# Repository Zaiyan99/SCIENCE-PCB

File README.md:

# SCIENCE-PCB
This a PCB made for URC 2023 on behalf of Mongol-Tori. It interfaces some sensors to decrease wire complexity

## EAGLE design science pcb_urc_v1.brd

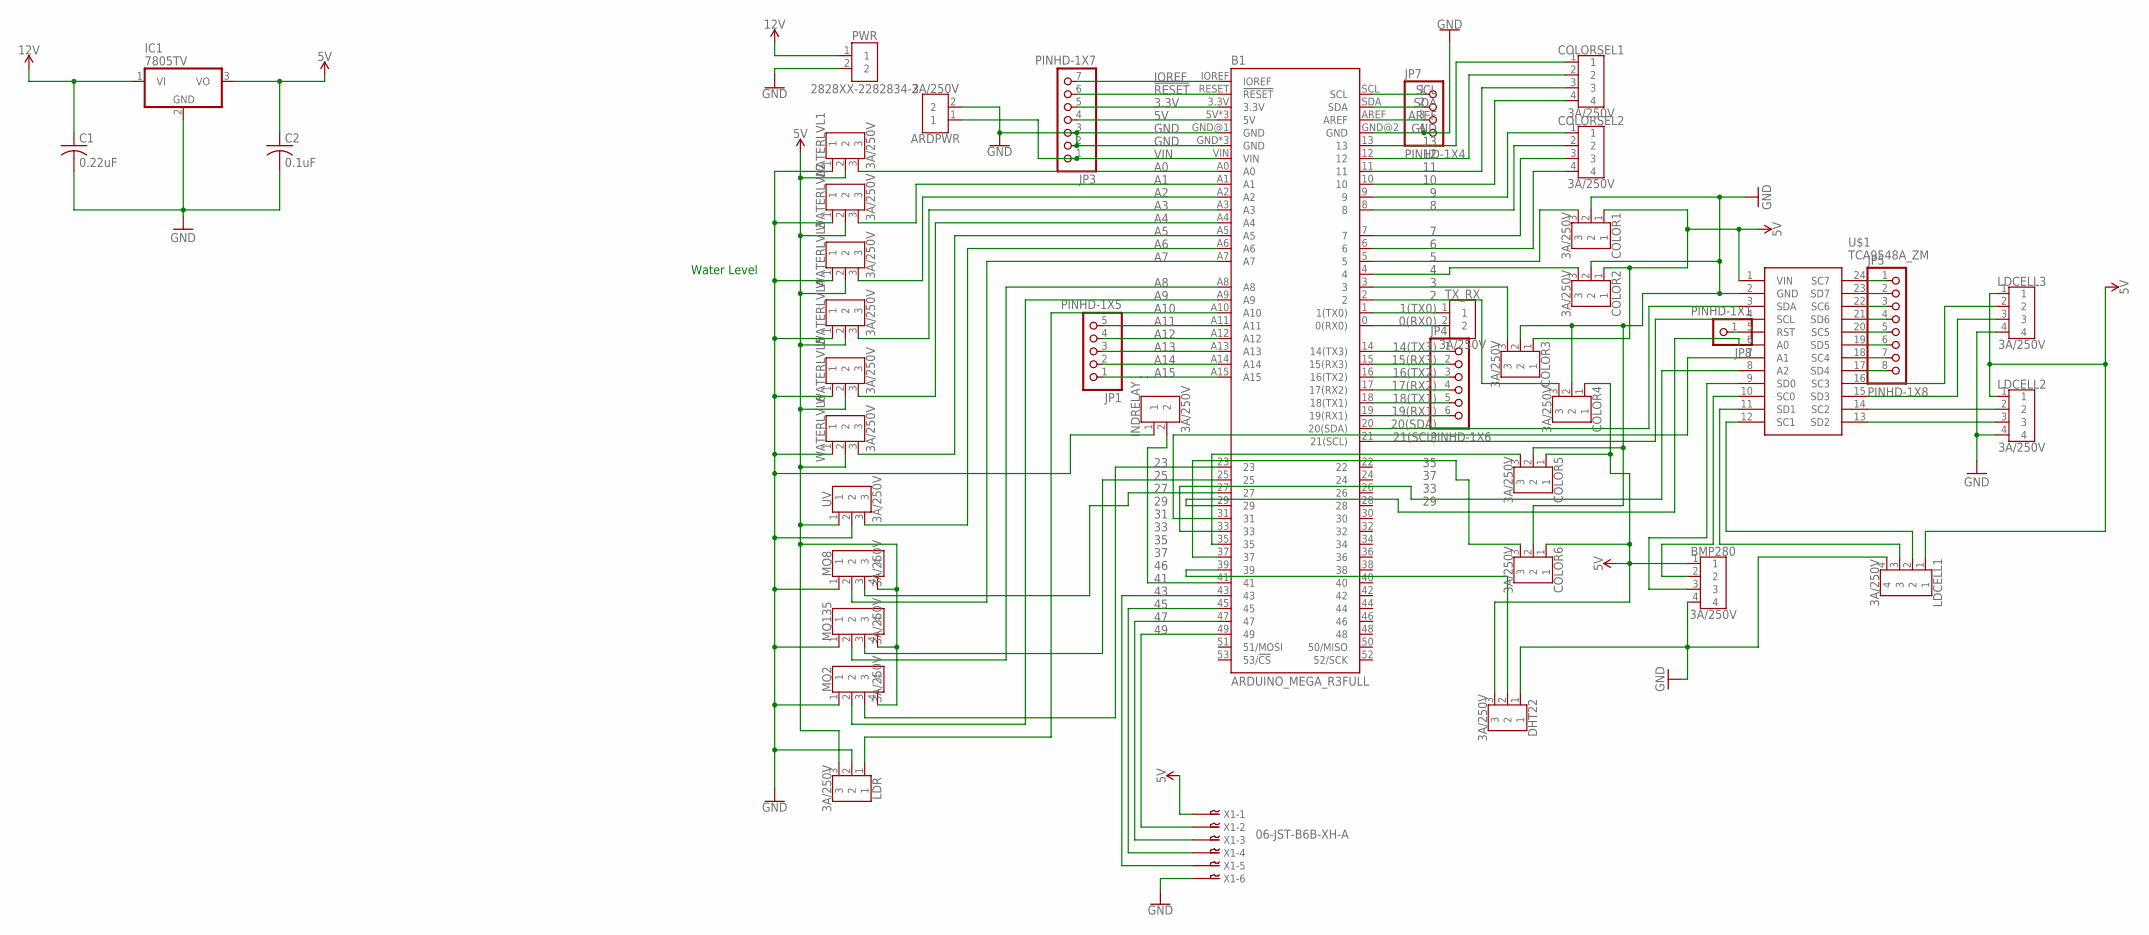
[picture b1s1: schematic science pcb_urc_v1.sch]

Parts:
ARDPWR: 3A/250V; B2B-XH-A
B1: ARDUINO_MEGA_R3FULL; ARDUINO_MEGA_NO_SILK
BMP280: 3A/250V; B4B-XH-A
C1: 0.22uF; C025-025X050
C2: 0.1uF; C025-025X050
COLOR1, COLOR2, COLOR3, COLOR4, COLOR5, COLOR6: 3A/250V; B3B-XH-A
COLORSEL1, COLORSEL2: 3A/250V; B4B-XH-A
DHT22: 3A/250V; B3B-XH-A
IC1: 7805TV; TO220V
INDRELAY: 3A/250V; B2B-XH-A
JP1: PINHD-1X5; 1X05
JP3: PINHD-1X7; 1X07
JP4: PINHD-1X6; 1X06
JP5: PINHD-1X8; 1X08
JP7: PINHD-1X4; 1X04
JP8: PINHD-1X1; 1X01
LDCELL1, LDCELL2, LDCELL3: 3A/250V; B4B-XH-A
LDR: 3A/250V; B3B-XH-A
MQ2, MQ8, MQ135: 3A/250V; B4B-XH-A
PWR: 2828XX-2282834-2; TERMBLK_254-2N
TX_RX: 3A/250V; B2B-XH-A
U$1: TCA9548A_ZM; 2717
UV: 3A/250V; B3B-XH-A
WATERLVL1, WATERLVL2, WATERLVL3, WATERLVL4, WATERLVL5, WATERLVL6: 3A/250V; B3B-XH-A
X1: 06-JST-B6B-XH-A; B6B-XH

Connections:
0(RX0): B1.0 (0(RX0)), TX_RX.2
1(TX0): B1.1 (1(TX0)), TX_RX.1
2: B1.2, COLOR4.3
3: B1.3, COLOR3.3
3.3V: B1.3.3V, JP3.5
4: B1.4, COLOR2.3
5: B1.5, COLOR1.3
5V: B1.5V, B1.5V@1 (5V), B1.5V@2 (5V), BMP280.1, C2.1, COLOR1.1, COLOR2.1, COLOR3.1, COLOR4.1, COLOR5.1, COLOR6.1, DHT22.3, IC1.3 (VO), JP3.4, LDCELL1.1, LDCELL2.1, LDCELL3.1, LDR.3, MQ2.4, MQ8.4, MQ135.4, U$1.1 (VIN), UV.1, WATERLVL1.2, WATERLVL2.2, WATERLVL3.2, WATERLVL4.2, WATERLVL5.2, WATERLVL6.2, X1.P$1
6: B1.6, COLORSEL2.4
7: B1.7, COLORSEL2.3
8: B1.8, COLORSEL2.2
9: B1.9, COLORSEL2.1
10: B1.10, COLORSEL1.4
11: B1.11, COLORSEL1.3
12: B1.12, COLORSEL1.2
12V: C1.1, IC1.1 (VI), PWR.1
13: B1.13, COLORSEL1.1
14(TX3): B1.14 (14(TX3)), JP4.1
15(RX3): B1.15 (15(RX3)), JP4.2
16(TX2): B1.16 (16(TX2)), JP4.3
17(RX2): B1.17 (17(RX2)), JP4.4
18(TX1): B1.18 (18(TX1)), JP4.5
19(RX1): B1.19 (19(RX1)), JP4.6
20(SDA): B1.20 (20(SDA)), U$1.3 (SDA)
21(SCL): B1.21 (21(SCL)), U$1.4 (SCL)
23: B1.27, MQ8.3
25: B1.25, MQ135.3
27: B1.23, MQ2.3
29: B1.29, U$1.6 (A0)
31: B1.31, U$1.7 (A1)
33: B1.33, U$1.8 (A2)
35: B1.35, COLOR5.3
37: B1.37, COLOR6.3
41: B1.41, INDRELAY.2
43: B1.43, X1.P$5
45: B1.45, X1.P$4
46: B1.39, DHT22.2
47: B1.47, X1.P$3
49: B1.49, X1.P$2
!RESET: B1.RESET (!RESET), JP3.6
A0: B1.A0, WATERLVL1.3
A1: B1.A1, WATERLVL2.3
A2: B1.A2, WATERLVL3.3
A3: B1.A3, WATERLVL4.3
A4: B1.A4, WATERLVL5.3
A5: B1.A5, WATERLVL6.3
A6: B1.A6, UV.3
A7: B1.A7, MQ8.2
A8: B1.A8, MQ135.2
A9: B1.A9, MQ2.2
A10: B1.A10, LDR.1
A11: B1.A11, JP1.5
A12: B1.A12, JP1.4
A13: B1.A13, JP1.3
A14: B1.A14, JP1.2
A15: B1.A15, JP1.1
AREF: B1.AREF, JP7.3
GND: ARDPWR.2, B1.GND, B1.GND@1 (GND), B1.GND@2 (GND), B1.GND@3 (GND), B1.GND@4 (GND), BMP280.4, C1.2, C2.2, COLOR1.2, COLOR2.2, COLOR3.2, COLOR4.2, COLOR5.2, COLOR6.2, DHT22.1, IC1.2 (GND), INDRELAY.1, JP3.2, JP3.3, JP7.4, LDCELL1.4, LDCELL2.4, LDCELL3.4, LDR.2, MQ2.1, MQ8.1, MQ135.1, PWR.2, U$1.2 (GND), UV.2, WATERLVL1.1, WATERLVL2.1, WATERLVL3.1, WATERLVL4.1, WATERLVL5.1, WATERLVL6.1, X1.P$6
IOREF: B1.IOREF, JP3.7
unnamed: LDCELL1.3, U$1.11 (SD1)
unnamed: LDCELL1.2, U$1.12 (SC1)
unnamed: LDCELL2.3, U$1.13 (SD2)
unnamed: LDCELL2.2, U$1.14 (SC2)
unnamed: LDCELL3.3, U$1.15 (SD3)
unnamed: LDCELL3.2, U$1.16 (SC3)
unnamed: JP8.1, U$1.5 (RST)
unnamed: JP5.1, U$1.24 (SC7)
unnamed: JP5.2, U$1.23 (SD7)
unnamed: JP5.3, U$1.22 (SC6)
unnamed: JP5.4, U$1.21 (SD6)
unnamed: JP5.5, U$1.20 (SC5)
unnamed: JP5.6, U$1.19 (SD5)
unnamed: JP5.7, U$1.18 (SC4)
unnamed: JP5.8, U$1.17 (SD4)
unnamed: BMP280.3, U$1.9 (SD0)
unnamed: BMP280.2, U$1.10 (SC0)
SCL: B1.SCL, JP7.1
SDA: B1.SDA, JP7.2
VIN: ARDPWR.1, B1.VIN, JP3.1

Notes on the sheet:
Water Level

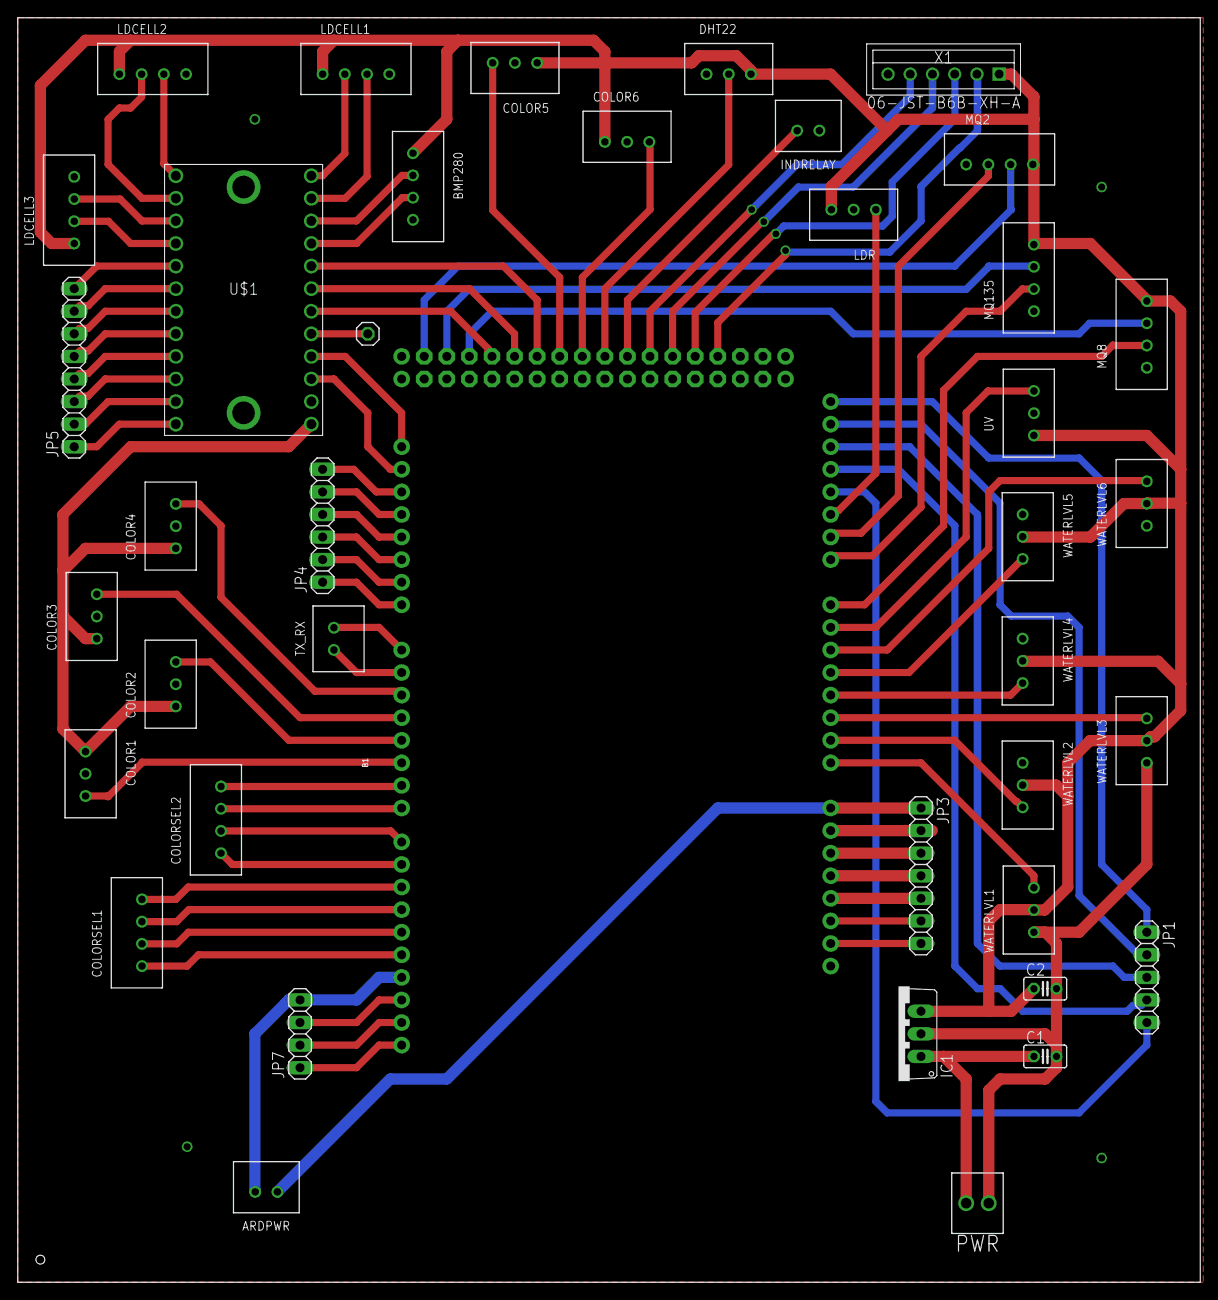
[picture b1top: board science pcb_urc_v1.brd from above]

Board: 2 copper layers, 133.0 x 142.2 mm, 40 parts (0 on the bottom side), 79 nets.

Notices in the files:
parts and their libraries:
SparkFun-Boards: Licensing: Creative Commons ShareAlike 4.0 International - https://creativecommons.org/licenses/by-sa/4.0
